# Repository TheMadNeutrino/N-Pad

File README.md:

N-Pad

The N-Pad is a 7-key macropad, equipped with a rotary encoder, OLED screen and 16 addressable LEDs. The heart of this pad is XIAO RP2040, controlled via KMK firmware.
N-Pad compounds of 3 main elements: PCB, Bottom (main) part of the case and the top part.

Features:

    -6 + 1 keys with awesome functions
    -Rotary encoder to modify volume and MUTE function when pressed (the 7th key).
    -128x32 OLED screen displaying the volume level
    -16 addressable LEDs (6 right under the keys and rest and the back side of PCB for even brighter and smoother backlight, fancy light at the USB port too)
    - Years of big software updates coming!

Model of the N-Pad:

The case is from 2 parts: The bottom part (includes space for PCB with raised platforms). The top has cutouts for key switches, rotary encoder as well as OLED screen and can be easily taken off.

Bottom part:

Top part (shown from the back side):

Thanks to the detachable design, no screws are needed for assembly.

Note: The first image shown a PCB with no parts on it, though contacts for keys visible. Designed in OnShape.

PCB:

PCB was designed in KiCad, consists of two layers.

Schematic:

PCB:

Firmware:

The N-Pad uses KMK firmware, loads of software updates coming, stay tuned!

Keys curretnly represents these functions: Copy, Paste, Homescreen, Play/Pause, Undo, Save

BOM:

    6 Cherry MX Switches

    6 DSA Keycaps
    
    6 1N4148 DO-35 Diodes.
    
    16 WS2812B LEDs 
    
    1 0.91" 128x32 OLED Display
    
    1 EC11 Rotary Encoder
    
    1 XIAO RP2040
    
    1 PCB
    
    1 Case (2 printed parts - detachable design - see CAD and Production folders)

Designed in the UK, (will be) assembled in the Czech Republic, EU, with parts from more than one country (living in the Czech Republic but currently on a UK trip)

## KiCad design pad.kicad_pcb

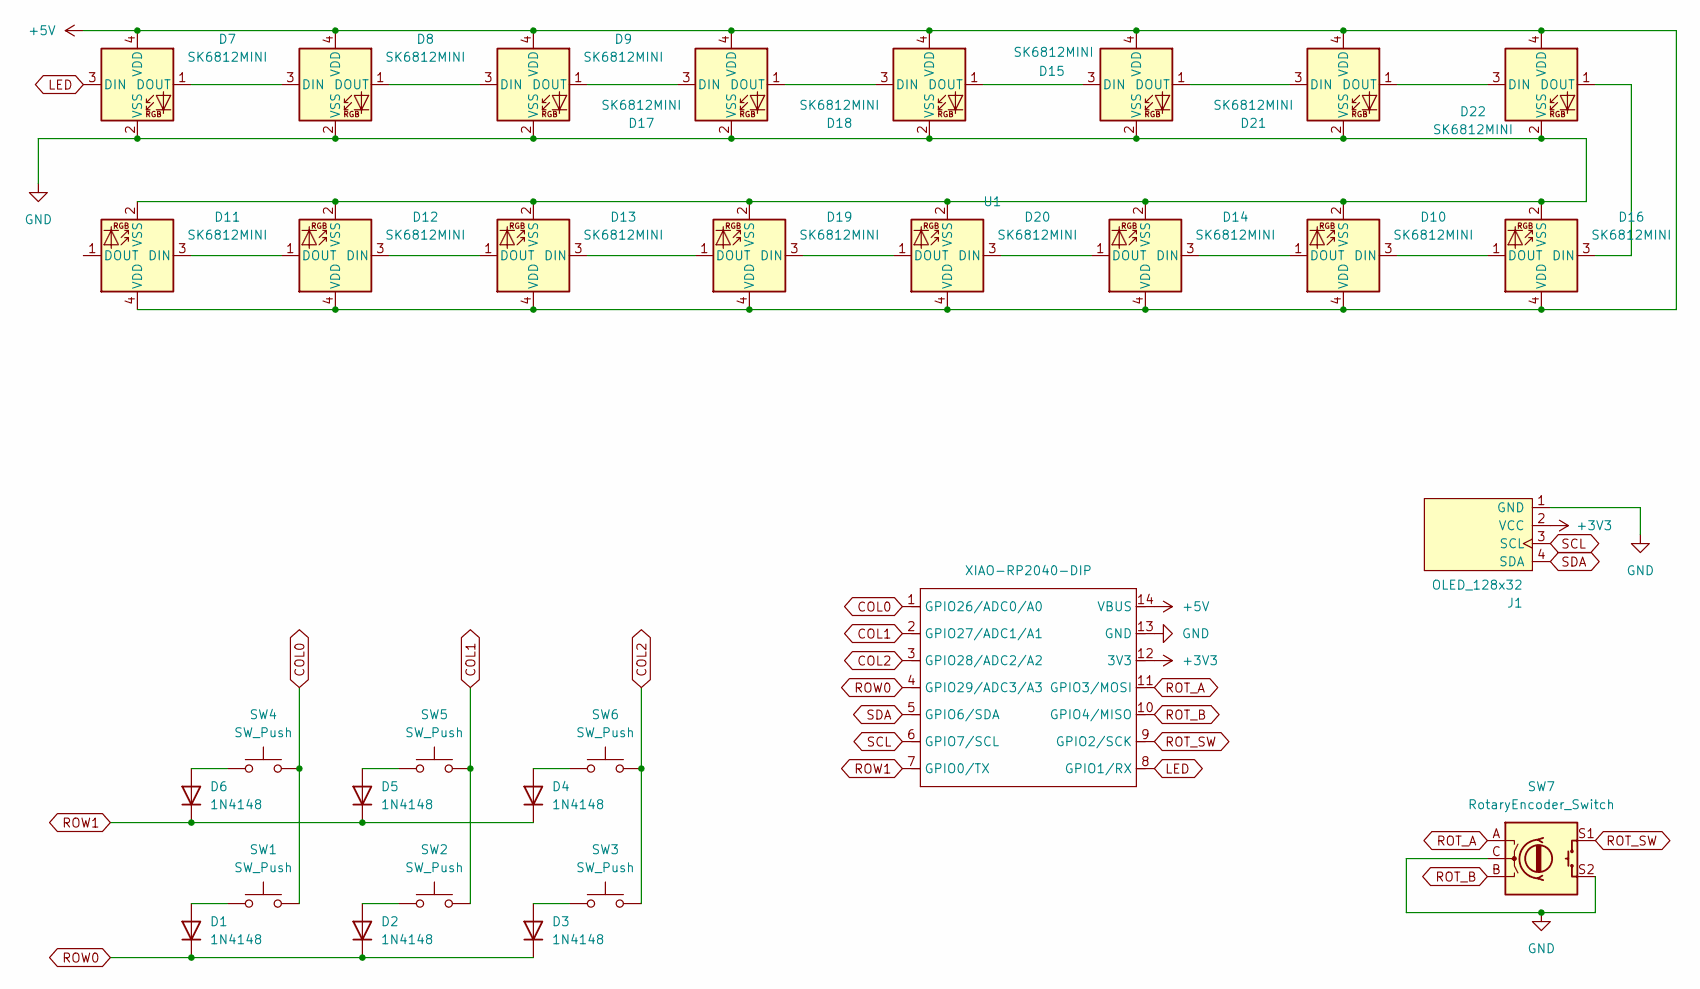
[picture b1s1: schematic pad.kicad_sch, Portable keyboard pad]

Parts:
D1, D2, D3, D4, D5, D6: 1N4148; D_DO-35_SOD27_P7.62mm_Horizontal
D7, D8, D9, D10, D11, D12, D13, D14, D15, D16, D17, D18, D19, D20, D21, D22: SK6812MINI; LED_SK6812MINI_PLCC4_3.5x3.5mm_P1.75mm
J1: OLED_128x32
SW1, SW2, SW3, SW4, SW5, SW6: SW_Push; SW_Cherry_MX_1.00u_PCB
SW7: RotaryEncoder_Switch; RotaryEncoder_Alps_EC11E-Switch_Vertical_H20mm
U1: XIAO-RP2040-DIP; XIAO-RP2040-SMD

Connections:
+3V3: J1.2 (VCC), U1.12 (3V3)
+5V: D7.4 (VDD), D8.4 (VDD), D9.4 (VDD), D10.4 (VDD), D11.4 (VDD), D12.4 (VDD), D13.4 (VDD), D14.4 (VDD), D15.4 (VDD), D16.4 (VDD), D17.4 (VDD), D18.4 (VDD), D19.4 (VDD), D20.4 (VDD), D21.4 (VDD), D22.4 (VDD), U1.14 (VBUS)
COL0: SW1.2, SW4.2, U1.1 (GPIO26/ADC0/A0)
COL1: SW2.2, SW5.2, U1.2 (GPIO27/ADC1/A1)
COL2: SW3.2, SW6.2, U1.3 (GPIO28/ADC2/A2)
GND: D7.2 (VSS), D8.2 (VSS), D9.2 (VSS), D10.2 (VSS), D11.2 (VSS), D12.2 (VSS), D13.2 (VSS), D14.2 (VSS), D15.2 (VSS), D16.2 (VSS), D17.2 (VSS), D18.2 (VSS), D19.2 (VSS), D20.2 (VSS), D21.2 (VSS), D22.2 (VSS), J1.1 (GND), SW7.C, SW7.S2, U1.13 (GND)
LED: D7.3 (DIN), U1.8 (GPIO1/RX)
unnamed: D1.2 (A), SW1.1
unnamed: D2.2 (A), SW2.1
unnamed: D3.2 (A), SW3.1
unnamed: D4.2 (A), SW6.1
unnamed: D5.2 (A), SW5.1
unnamed: D6.2 (A), SW4.1
unnamed: D7.1 (DOUT), D8.3 (DIN)
unnamed: D8.1 (DOUT), D9.3 (DIN)
unnamed: D10.3 (DIN), D16.1 (DOUT)
unnamed: D10.1 (DOUT), D14.3 (DIN)
unnamed: D11.3 (DIN), D12.1 (DOUT)
unnamed: D12.3 (DIN), D13.1 (DOUT)
unnamed: D13.3 (DIN), D19.1 (DOUT)
unnamed: D14.1 (DOUT), D20.3 (DIN)
unnamed: D15.3 (DIN), D18.1 (DOUT)
unnamed: D15.1 (DOUT), D21.3 (DIN)
unnamed: D16.3 (DIN), D22.1 (DOUT)
unnamed: D9.1 (DOUT), D17.3 (DIN)
unnamed: D17.1 (DOUT), D18.3 (DIN)
unnamed: D19.3 (DIN), D20.1 (DOUT)
unnamed: D21.1 (DOUT), D22.3 (DIN)
ROT_A: SW7.A, U1.11 (GPIO3/MOSI)
ROT_B: SW7.B, U1.10 (GPIO4/MISO)
ROT_SW: SW7.S1, U1.9 (GPIO2/SCK)
ROW0: D1.1 (K), D2.1 (K), D3.1 (K), U1.4 (GPIO29/ADC3/A3)
ROW1: D4.1 (K), D5.1 (K), D6.1 (K), U1.7 (GPIO0/TX)
SCL: J1.3 (SCL), U1.6 (GPIO7/SCL)
SDA: J1.4 (SDA), U1.5 (GPIO6/SDA)

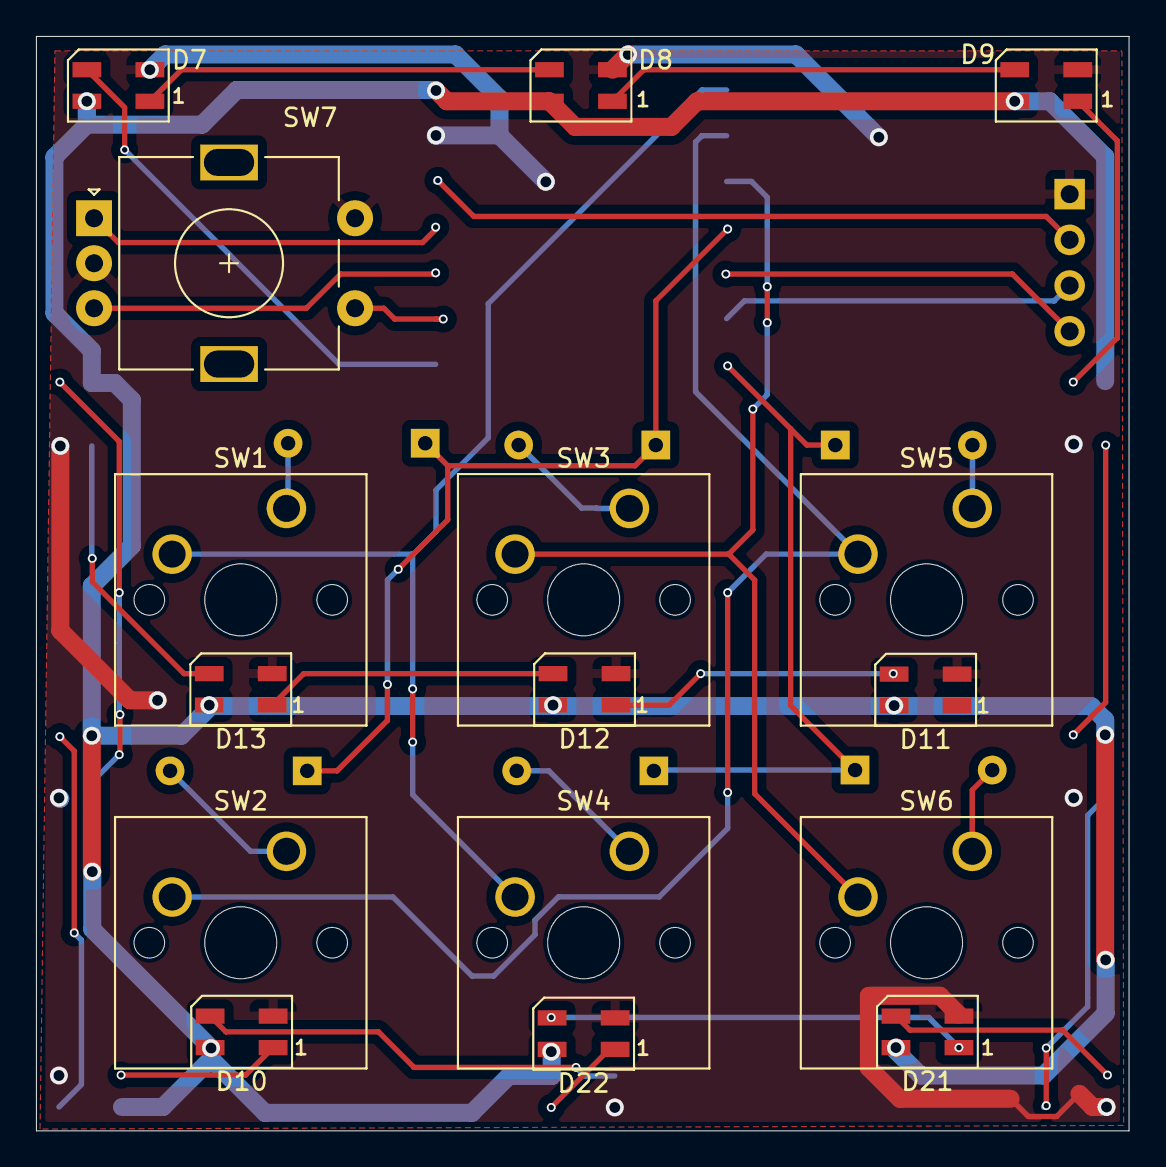
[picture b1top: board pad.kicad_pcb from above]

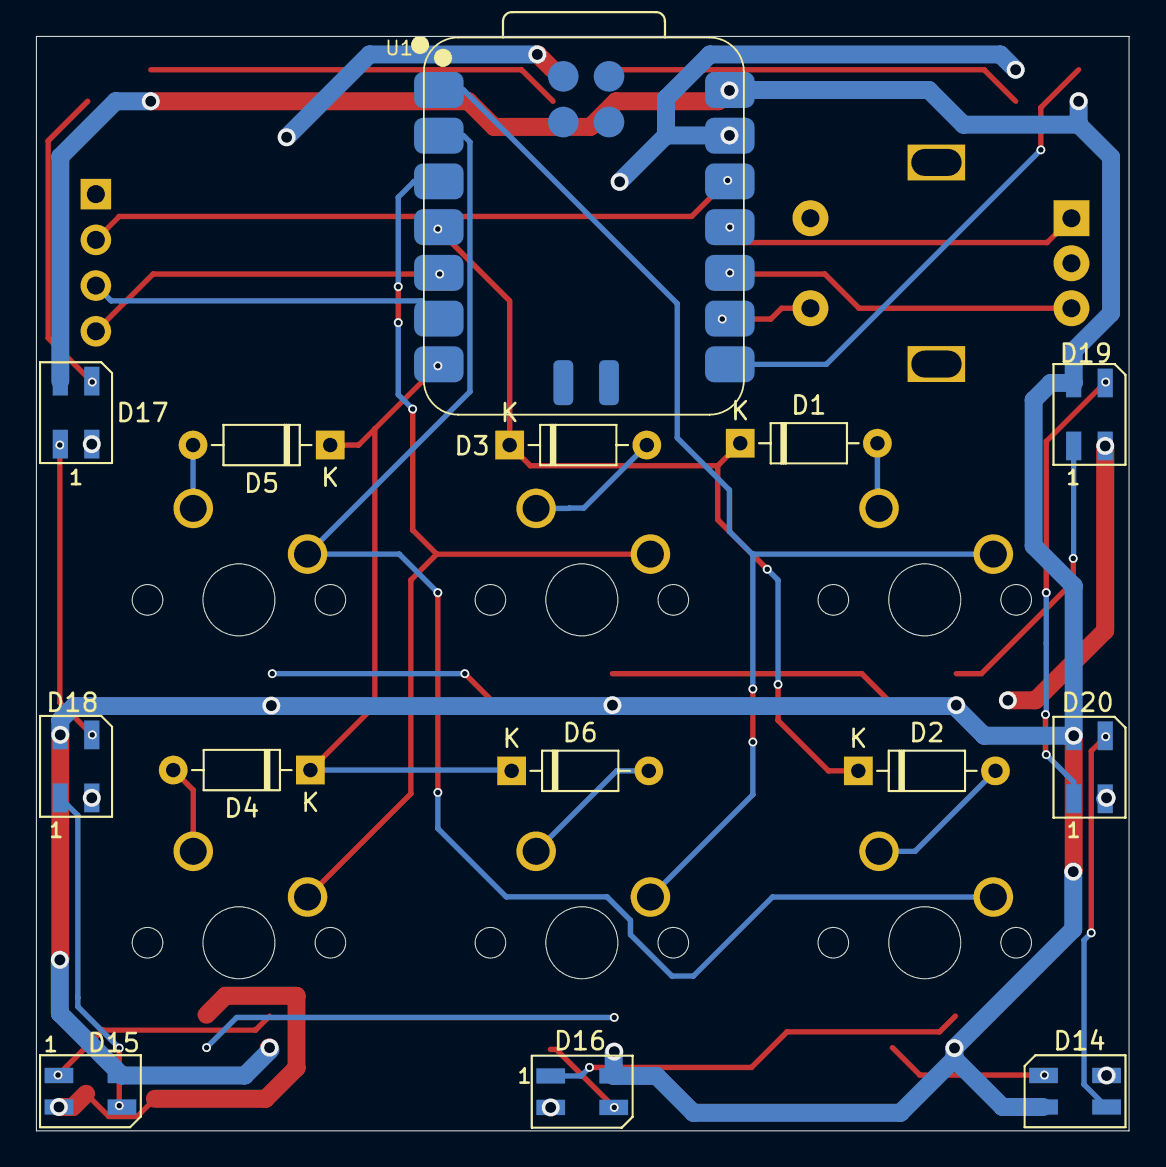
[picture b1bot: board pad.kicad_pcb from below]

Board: 2 copper layers, 60.7 x 60.8 mm, 31 parts (14 on the bottom side), 35 nets.
